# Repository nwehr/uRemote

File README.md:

# uRemote

uRemote is a general purpose IR/USB remote. There are two inputs:

1. Rotary Encoder
2. Momentary Switch

Currently, the firmware transmits IR NEC-encoded volume and power signals to a Visio V405-G9 tv.

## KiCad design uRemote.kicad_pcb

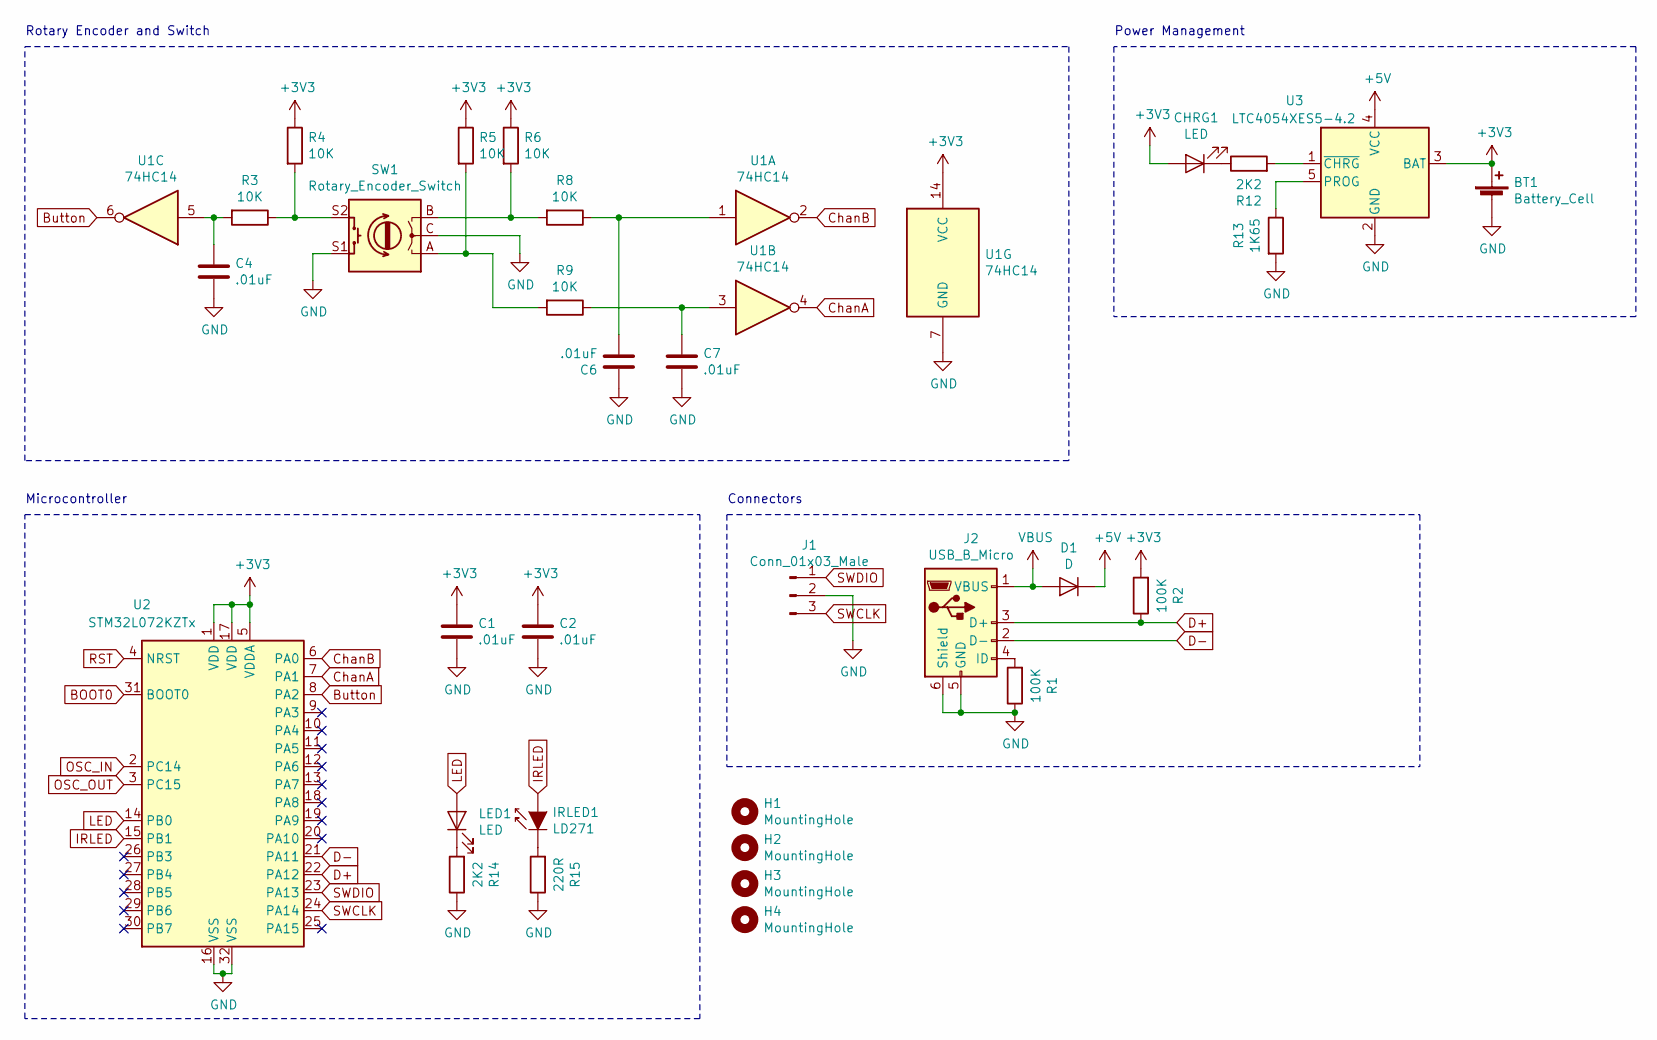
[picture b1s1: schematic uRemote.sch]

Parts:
BT1: Battery_Cell; BatteryHolder_Keystone_103_1x20mm
C1, C2, C4, C6, C7: .01uF; C_0805_2012Metric
CHRG1: LED; LED_0805_2012Metric
D1: D; D_0805_2012Metric
H1, H2, H3, H4: MountingHole; MountingHole_2.2mm_M2_Pad_Via
IRLED1: LD271; LED_Wurth_2.6x0.84mm
J1: Conn_01x03_Male; PinHeader_1x03_P2.54mm_Vertical
J2: USB_B_Micro; USB_Micro-B_Molex_47346-0001
LED1: LED; LED_0805_2012Metric
R1, R2: 100K; R_0805_2012Metric
R3, R4, R5, R6, R8, R9: 10K; R_0805_2012Metric
R12, R14: 2K2; R_0805_2012Metric
R13: 1K65; R_0805_2012Metric
R15: 220R; R_0805_2012Metric
SW1: Rotary_Encoder_Switch; RotaryEncoder_Alps_EC11E-Switch_Vertical_H20mm
U1: 74HC14; SOIC-14_3.9x8.7mm_P1.27mm
U2: STM32L072KZTx; LQFP-32_7x7mm_P0.8mm
U3: LTC4054XES5-4.2; TSOT-23-5

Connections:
+3V3: BT1.1 (+), C1.1, C2.1, CHRG1.2 (A), R2.2, R4.1, R5.1, R6.1, U1.14 (VCC), U2.1 (VDD), U2.5 (VDDA), U2.17 (VDD), U3.3 (BAT); also elsewhere on the board
+5V: D1.1 (K), U3.4 (VCC)
BOOT0: U2.31 (BOOT0)
Button: U1.6, U2.8 (PA2)
ChanA: U1.4, U2.7 (PA1)
ChanB: U1.2, U2.6 (PA0)
D+: J2.3 (D+), R2.1, U2.22 (PA12)
D-: J2.2 (D-), U2.21 (PA11)
GND: BT1.2 (-), C1.2, C2.2, C4.2, C6.1, C7.2, J1.2, J2.5 (GND), J2.6 (Shield), R1.1, R13.2, R14.1, R15.1, SW1.C, SW1.S1, U1.7 (GND), U2.16 (VSS), U2.32 (VSS), U3.2 (GND)
IRLED: IRLED1.2 (A), U2.15 (PB1)
LED: LED1.2 (A), U2.14 (PB0)
unnamed: C4.1, R3.2, U1.5
unnamed: C6.2, R8.1, U1.1
unnamed: C7.1, R9.1, U1.3
unnamed 14: CHRG1.1 (K), R12.1; also elsewhere on the board
unnamed: IRLED1.1 (K), R15.2
unnamed: J2.4 (ID), R1.2
unnamed: LED1.1 (K), R14.2
unnamed: R3.1, R4.2, SW1.S2
unnamed: R5.2, R9.2, SW1.A
unnamed: R6.2, R8.2, SW1.B
unnamed: R12.2, U3.1 (~CHRG)
unnamed: R13.1, U3.5 (PROG)
OSC_IN: U2.2 (PC14)
OSC_OUT: U2.3 (PC15)
RST: U2.4 (NRST)
SWCLK: J1.3, U2.24 (PA14)
SWDIO: J1.1, U2.23 (PA13)
VBUS: D1.2 (A), J2.1 (VBUS)

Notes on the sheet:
Rotary Encoder and Switch
Connectors
Power Management
Microcontroller

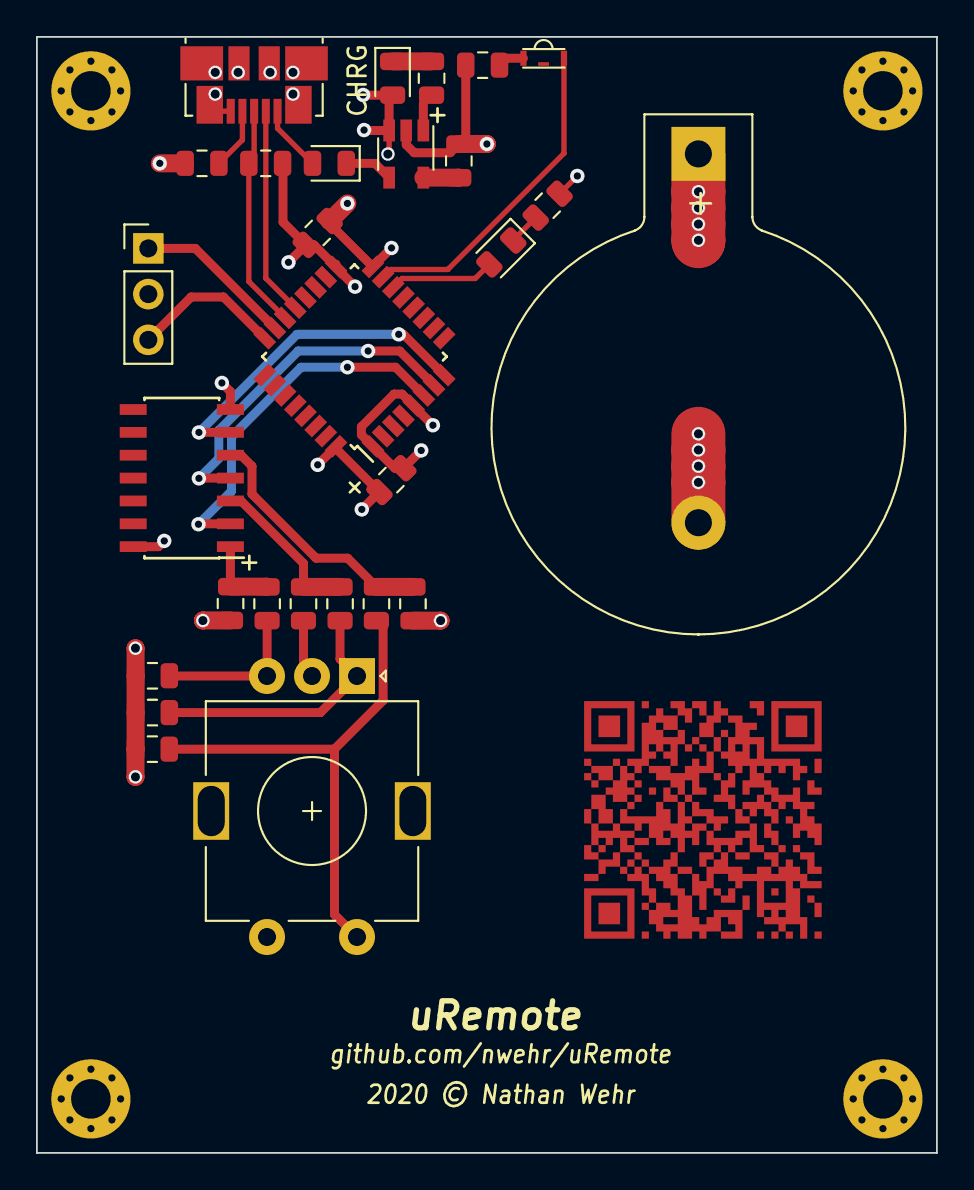
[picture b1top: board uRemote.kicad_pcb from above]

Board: 4 copper layers, 50.0 x 62.0 mm, 33 parts (0 on the bottom side), 25 nets.

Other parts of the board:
CHRG: LED; LED_0805_2012Metric
QR*****: github_com_nwehr_uRemote

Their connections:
+3V3: CHRG.2; also elsewhere on the board
unnamed 14: CHRG.1; also elsewhere on the board

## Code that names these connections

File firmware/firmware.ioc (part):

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Mcu.UserName=STM32L072KZTx
PA0.GPIO_Label=Chan_B
PA11.Mode=Device
PB0.GPIO_Label=LED
PA2.GPIOParameters=GPIO_Label
RCC.SYSCLKSource=RCC_SYSCLKSOURCE_HSI
PA13.Signal=SYS_SWDIO
PA12.Signal=USB_DP
PA1.Signal=GPXTI1
board=custom
PB0.GPIOParameters=GPIO_Label
PA1.GPIOParameters=GPIO_Label
PA14.Mode=Serial_Wire
PB1.GPIO_Label=IR_LED
PA1.GPIO_Label=Chan_A
PA10.GPIO_Label=VBUS_SENSE
PA10.GPIOParameters=GPIO_Label
PB7.Signal=SYS_PVD_IN
PA13.Mode=Serial_Wire
Mcu.Name=STM32L072K(B-Z)Tx
PA2.Signal=GPXTI2
PA0.Signal=GPXTI0
RCC.SYSCLKFreq_VALUE=16000000
Mcu.Package=LQFP32
PB1.Signal=GPIO_Output
PA12.Mode=Device
PA2.GPIO_Label=Button
PB7.Mode=Mode_PVD_Ext
PA11.Signal=USB_DM
PA10.Signal=GPIO_Input
PA14.Signal=SYS_SWCLK
PA0.GPIOParameters=GPIO_Label
PB0.Signal=GPIO_Output
PB1.GPIOParameters=GPIO_Label

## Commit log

2020-08-28 Added Readme

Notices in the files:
uRemote.kicad_pcb:
2020 © Nathan Wehr
